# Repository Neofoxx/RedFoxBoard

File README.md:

# RedFoxBoard
A PIC32MX250 (and others) board, similar to the ubiquitous Blue Pill board

## Pinout

#### PCB view

#### Panel view

## Description 

This is a small development board, featured around a PIC32MX microcontroller.

The intent is to have a small Blue Pill-like board, that can be quickly used with an open-source toolchain for the PIC32MX (see https://gitlab.com/rhn/pic32-parts-free )

The feature list is as follows:
- USB-C connector
- Two LEDs, one Power, one User
- Two buttons, one Reset, one User
- Components only on one side
- Footprints for two 3.3V regulators (smaller or bigger, depending on your needs)
- Fits into DIP-40 socket
- Breakaway section on the PCB, with place for an ICSP or JTAG connector

The purpose of the breakaway is to have a convenient place for programming/debugging. The same pins are also exposed on the side pins. To remove the breakaway, score the vias with a knife, then break it off.

Apart from the oscillator pins, everything is connected to the side pins.

If you do not wish to use USB functionality, you can place resistors R9 and R10, and connect those pins to the side as well.

### Supported MCUs
It supports the following microcontrollers:
- PIC32MX270F256D
- PIC32MX250F128D
- PIC32MX230F256D
- PIC32MX230F064D
- PIC32MX170F256D (without USB)
- PIC32MX150F128D (without USB)
- PIC32MX130F256D (without USB)
- PIC32MX130F064D (without USB)

Additionally, the following can also be used, but ICSP pins are not available on the provided header (use the ones on the side):
- PIC32MX220F032D
- PIC32MX210F016D
- PIC32MX120F032D (without USB)
- PIC32MX110F016D (without USB)

#### Notes

Please note, there are 6mm push buttons with different spacings on the pins. Make sure to get the right ones

The series resistor with the main oscillator hasn't been checked yet

The capacitors for the 32.768kHz crystal haven't been checked yet.

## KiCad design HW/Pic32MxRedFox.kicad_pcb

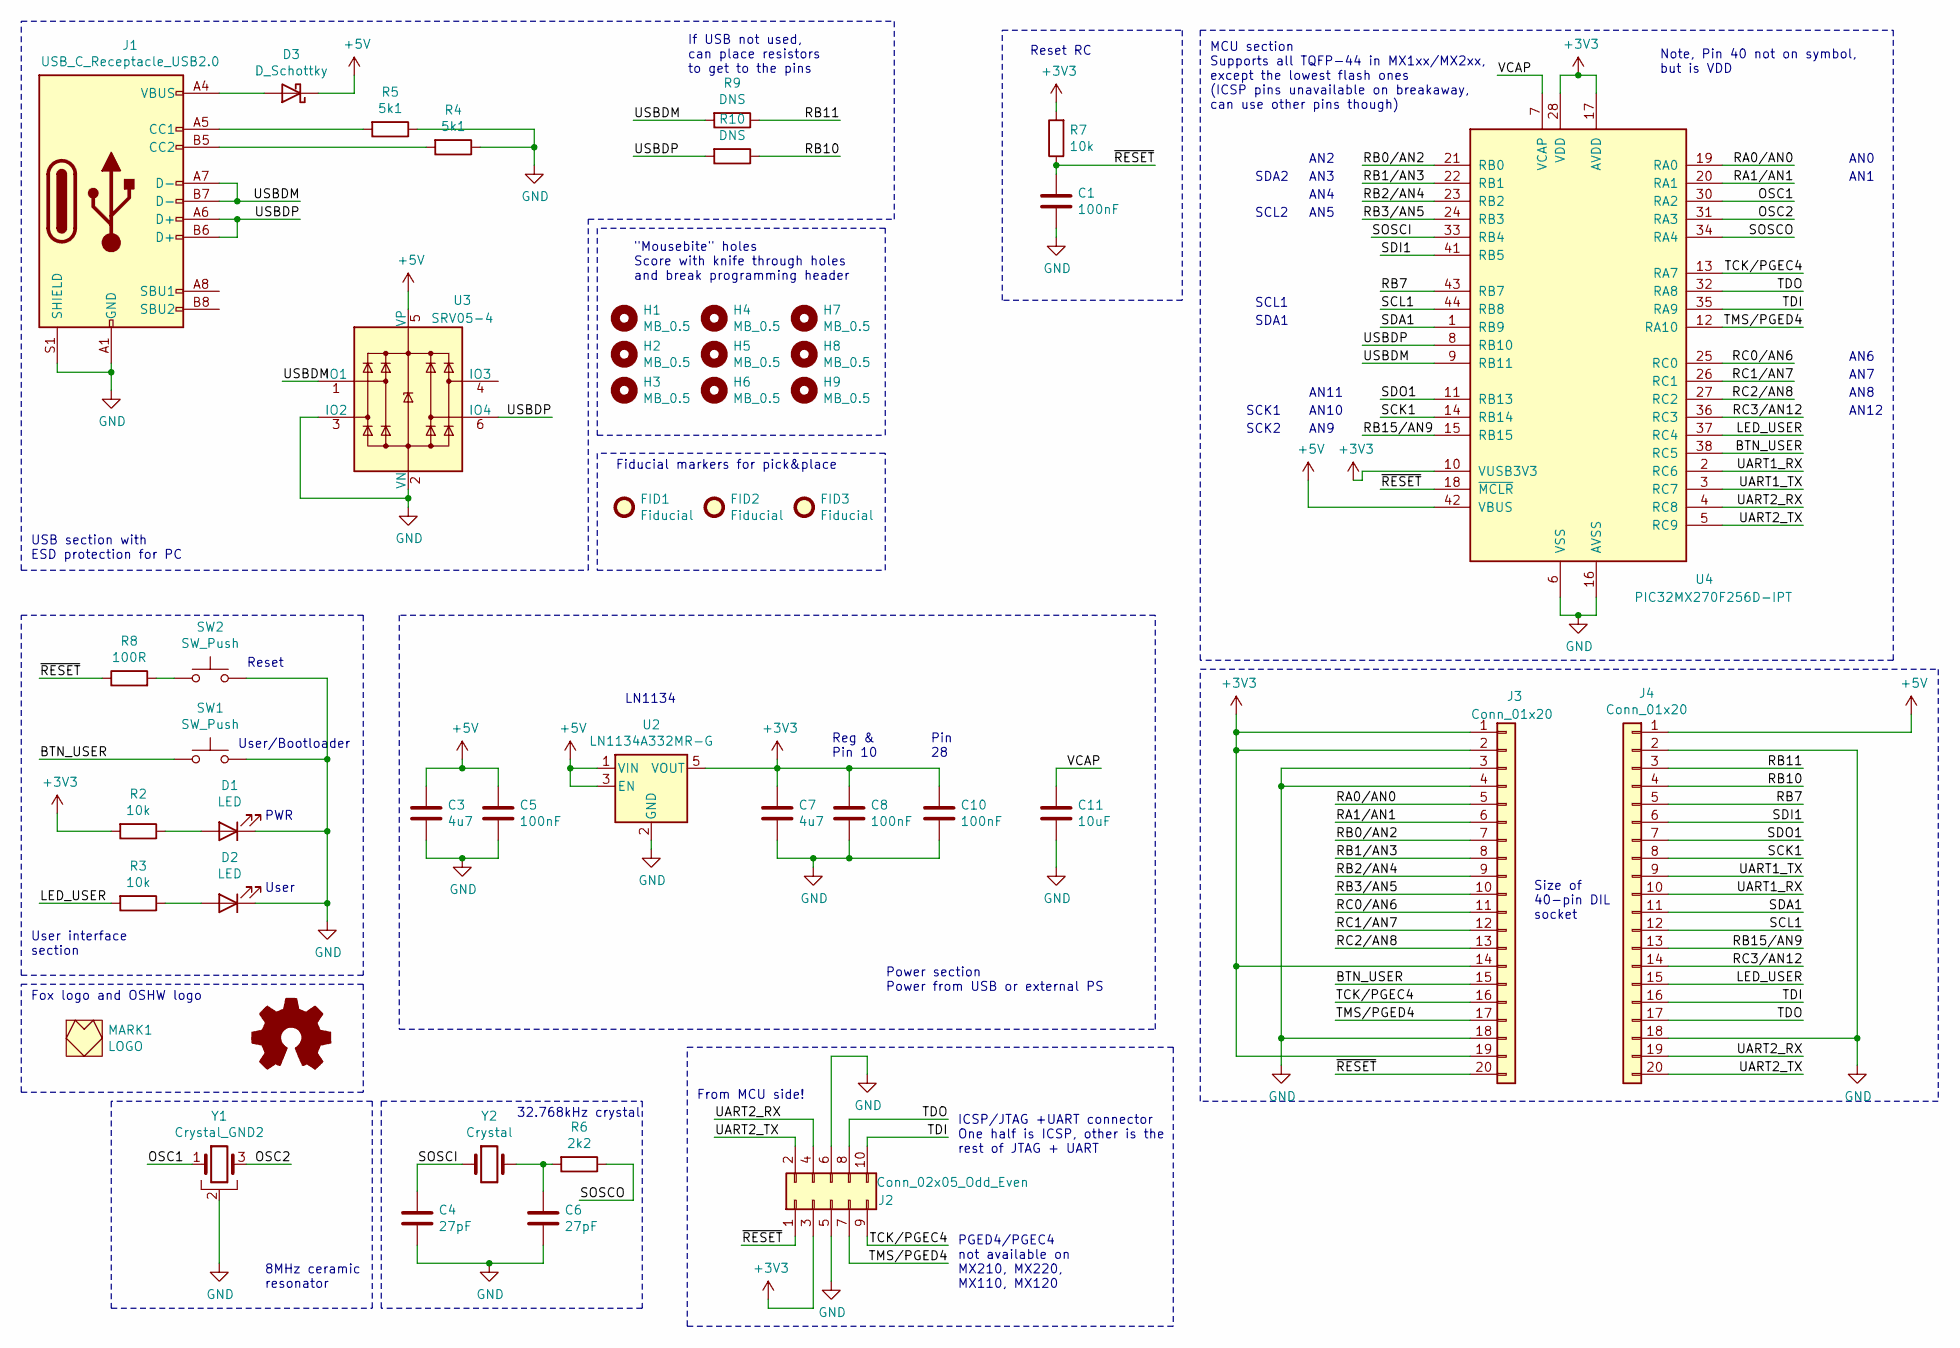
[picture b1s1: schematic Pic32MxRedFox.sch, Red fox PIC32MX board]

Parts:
C1, C5, C8, C10: 100nF; C_0603_1608Metric_Pad1.05x0.95mm_HandSolder
C3, C7: 4u7; C_0805_2012Metric_Pad1.15x1.40mm_HandSolder
C4, C6: 27pF; C_0603_1608Metric_Pad1.05x0.95mm_HandSolder
C11: 10uF; C_0805_2012Metric_Pad1.15x1.40mm_HandSolder
D1, D2: LED; LED_0603_1608Metric_Pad1.05x0.95mm_HandSolder
D3: D_Schottky; D_SOD-323_HandSoldering
FID1, FID2, FID3: Fiducial; Fiducial_0.5mm_Mask1mm
H1, H2, H3, H4, H5, H6, H7, H8, H9: MB_0.5; MouseBiteHole_0.5mm
J1: USB_C_Receptacle_USB2.0; Jing USB C 2.0 16pin receptable
J2: Conn_02x05_Odd_Even; IDC-Header_2x05_P2.54mm_Vertical
J3, J4: Conn_01x20; PinHeader_1x20_P2.54mm_Vertical
MARK1: LOGO; FOX_LOGO_MASK
MARK2: Logo_Open_Hardware_Small; OSHW-Logo_5.7x6mm_SilkScreen
R2, R3, R7: 10k; R_0603_1608Metric_Pad1.05x0.95mm_HandSolder
R4, R5: 5k1; R_0603_1608Metric_Pad1.05x0.95mm_HandSolder
R6: 2k2; R_0603_1608Metric_Pad1.05x0.95mm_HandSolder
R8: 100R; R_0603_1608Metric_Pad1.05x0.95mm_HandSolder
R9, R10: DNS; R_0603_1608Metric_Pad1.05x0.95mm_HandSolder
SW1, SW2: SW_Push; SW_SPST_B3S-1000
U2: LN1134A332MR-G; SOT-23-5
U3: SRV05-4; SOT-23-6
U4: PIC32MX270F256D-IPT; TQFP-44_10x10mm_P0.8mm
Y1: Crystal_GND2; Resonator_SMD_muRata_CSTxExxV-3Pin_3.0x1.1mm
Y2: Crystal; Crystal_SMD_3215-2Pin_3.2x1.5mm

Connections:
+3V3: C7.1, C8.1, C10.1, J2.3, J3.1, J3.2, J3.14, J3.19, R2.2, R7.2, U2.5 (VOUT), U4.10 (VUSB3V3), U4.17 (AVDD), U4.28 (VDD), U4.40 (VDD)
+5V: C3.1, C5.1, D3.1 (K), J4.1, U2.1 (VIN), U2.3 (EN), U3.5 (VP), U4.42 (VBUS)
/BTN_USER: J3.15, SW1.1, U4.38 (RC5)
/LED_USER: J4.15, R3.2, U4.37 (RC4)
/OSC1: U4.30 (RA2), Y1.1
/OSC2: U4.31 (RA3), Y1.3
/RA0/AN0: J3.5, U4.19 (RA0)
/RA1/AN1: J3.6, U4.20 (RA1)
/RB0/AN2: J3.7, U4.21 (RB0)
/RB1/AN3: J3.8, U4.22 (RB1)
/RB2/AN4: J3.9, U4.23 (RB2)
/RB3/AN5: J3.10, U4.24 (RB3)
/RB7: J4.5, U4.43 (RB7)
/RB10: J4.4, R10.1
/RB11: J4.3, R9.1
/RB15/AN9: J4.13, U4.15 (RB15)
/RC0/AN6: J3.11, U4.25 (RC0)
/RC1/AN7: J3.12, U4.26 (RC1)
/RC2/AN8: J3.13, U4.27 (RC2)
/RC3/AN12: J4.14, U4.36 (RC3)
/SCK1: J4.8, U4.14 (RB14)
/SCL1: J4.12, U4.44 (RB8)
/SDA1: J4.11, U4.1 (RB9)
/SDI1: J4.6, U4.41 (RB5)
/SDO1: J4.7, U4.11 (RB13)
/SOSCI: C4.1, U4.33 (RB4), Y2.1
/SOSCO: R6.1, U4.34 (RA4)
/TCK/PGEC4: J2.9, J3.16, U4.13 (RA7)
/TDI: J2.10, J4.16, U4.35 (RA9)
/TDO: J2.8, J4.17, U4.32 (RA8)
/TMS/PGED4: J2.7, J3.17, U4.12 (RA10)
/UART1_RX: J4.10, U4.2 (RC6)
/UART1_TX: J4.9, U4.3 (RC7)
/UART2_RX: J2.4, J4.19, U4.4 (RC8)
/UART2_TX: J2.2, J4.20, U4.5 (RC9)
/USBDM: J1.A7 (D-), J1.B7 (D-), R9.2, U3.1 (IO1), U4.9 (RB11)
/USBDP: J1.A6 (D+), J1.B6 (D+), R10.2, U3.6 (IO4), U4.8 (RB10)
/VCAP: C11.1, U4.7 (VCAP)
/~RESET~: C1.1, J2.1, J3.20, R7.1, R8.1, U4.18 (~MCLR)
GND: C1.2, C3.2, C4.2, C5.2, C6.2, C7.2, C8.2, C10.2, C11.2, D1.1 (K), D2.1 (K), J1.A1 (GND), J1.A12 (GND), J1.B1 (GND), J1.B12 (GND), J1.S1 (SHIELD), J2.5, J2.6, J3.3, J3.4, J3.18, J4.2, J4.18, R4.1, R5.1, SW1.2, SW2.2, U2.2 (GND), U3.2 (VN), U3.3 (IO2), U4.6 (VSS), U4.16 (AVSS), U4.29 (VSS), U4.39 (VSS), Y1.2
unnamed: C6.1, R6.2, Y2.2
unnamed: D1.2 (A), R2.1
unnamed: D2.2 (A), R3.1
unnamed: D3.2 (A), J1.A4 (VBUS), J1.A9 (VBUS), J1.B4 (VBUS), J1.B9 (VBUS)
unnamed: J1.A5 (CC1), R5.2
unnamed: J1.B5 (CC2), R4.2
unnamed: R8.2, SW2.1

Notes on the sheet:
Reset
User/Bootloader
PWR
User
Size of 40-pin DIL socket
ICSP/JTAG +UART connector One half is ICSP, other is the rest of JTAG + UART
From MCU side!
32.768kHz crystal
8MHz ceramic resonator
Reg & Pin 10
Pin 28
PGED4/PGEC4 not available on MX210, MX220, MX110, MX120
AN0
AN1
AN2
AN3
AN4
AN5
AN6
AN7
AN8
AN9
AN10
AN11
AN12
SDA1
SDA2
SCK1
SCK2
SCL1
SCL2
LN1134
If USB not used, can place resistors to get to the pins
User interface section
Power section Power from USB or external PS
MCU section Supports all TQFP-44 in MX1xx/MX2xx, except the lowest flash ones (ICSP pins unavailable on breakaway, can use other pins though)
Note, Pin 40 not on symbol, but is VDD
Reset RC
USB section with ESD protection for PC
"Mousebite" holes Score with knife through holes and break programming header

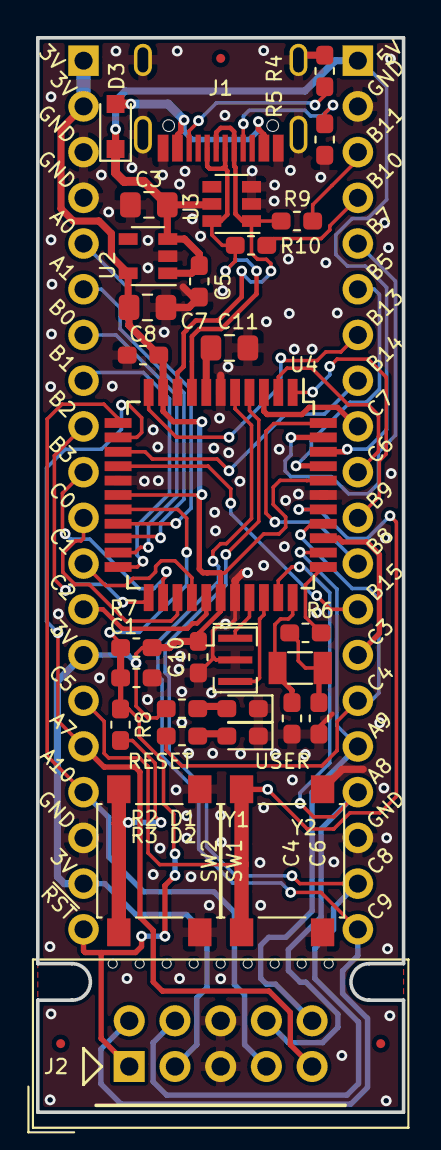
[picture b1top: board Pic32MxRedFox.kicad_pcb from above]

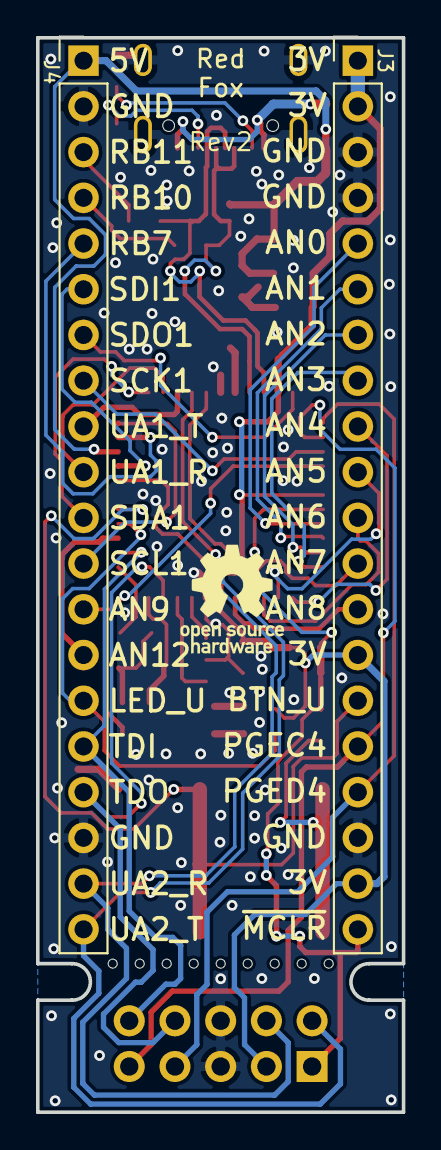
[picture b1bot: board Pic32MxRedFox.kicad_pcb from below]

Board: 2 copper layers, 20.3 x 59.7 mm, 46 parts (4 on the bottom side), 47 nets.

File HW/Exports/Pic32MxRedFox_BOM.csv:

"Source:","/home/neofoxx/Projects/HW/Gitted/RedFoxBoard/HW/Pic32MxRedFox.sch"
"Date:","pon 12 avg 2019 22:32:37 CEST"
"Tool:","Eeschema 5.0.2-bee76a0~70~ubuntu18.04.1"
"Generator:","/usr/share/kicad/plugins/bom_csv_grouped_by_value_with_fp.py"
"Component Count:","42"
"Ref","Qnty","Value","Cmp name","Footprint","Description","Vendor"
"C3, C7, ","2","4u7","C","Capacitor_SMD:C_0805_2012Metric_Pad1.15x1.40mm_HandSolder","Unpolarized capacitor",""
"C4, C6, ","2","27pF","C","Capacitor_SMD:C_0603_1608Metric_Pad1.05x0.95mm_HandSolder","Unpolarized capacitor",""
"C5, C8, C10, C9, C1, ","5","100nF","C","Capacitor_SMD:C_0603_1608Metric_Pad1.05x0.95mm_HandSolder","Unpolarized capacitor",""
"C11, ","1","10uF","C","Capacitor_SMD:C_0805_2012Metric_Pad1.15x1.40mm_HandSolder","Unpolarized capacitor",""
"D1, D2, ","2","LED","LED","LED_SMD:LED_0603_1608Metric_Pad1.05x0.95mm_HandSolder","Light emitting diode",""
"D3, ","1","D_Schottky","D_Schottky","Diode_SMD:D_SOD-323_HandSoldering","Schottky diode",""
"H1, H3, H5, H2, H4, H6, ","6","MB_0.5","MountingHole","KiCAD library:MouseBiteHole_0.5mm","Mounting Hole without connection",""
"J1, ","1","USB_C_Receptacle_USB2.0","USB_C_Receptacle_USB2.0","KiCAD library:Jing USB C 2.0 16pin receptable","USB 2.0-only Type-C Receptacle connector",""
"J2, ","1","Conn_02x05_Odd_Even","Conn_02x05_Odd_Even","Connector_IDC:IDC-Header_2x05_P2.54mm_Vertical","Generic connector, double row, 02x05, odd/even pin numbering scheme (row 1 odd numbers, row 2 even numbers), script generated (kicad-library-utils/schlib/autogen/connector/)",""
"J3, J4, ","2","Conn_01x20","Conn_01x20","Connector_PinHeader_2.54mm:PinHeader_1x20_P2.54mm_Vertical","Generic connector, single row, 01x20, script generated (kicad-library-utils/schlib/autogen/connector/)",""
"MARK1, ","1","LOGO","LOGO","KiCAD library:FOX_LOGO_MASK","",""
"R1, ","1","0R","R","Resistor_SMD:R_0603_1608Metric_Pad1.05x0.95mm_HandSolder","Resistor",""
"R2, R3, ","2","1k","R","Resistor_SMD:R_0603_1608Metric_Pad1.05x0.95mm_HandSolder","Resistor",""
"R4, R5, ","2","5k1","R","Resistor_SMD:R_0603_1608Metric_Pad1.05x0.95mm_HandSolder","Resistor",""
"R6, ","1","2k2","R","Resistor_SMD:R_0603_1608Metric_Pad1.05x0.95mm_HandSolder","Resistor",""
"R7, ","1","10k","R","Resistor_SMD:R_0603_1608Metric_Pad1.05x0.95mm_HandSolder","Resistor",""
"R8, ","1","100R","R","Resistor_SMD:R_0603_1608Metric_Pad1.05x0.95mm_HandSolder","Resistor",""
"R9, R10, ","2","DNS","R","Resistor_SMD:R_0603_1608Metric_Pad1.05x0.95mm_HandSolder","Resistor",""
"SW1, SW2, ","2","SW_Push","SW_Push","Button_Switch_SMD:SW_SPST_B3S-1000","Push button switch, generic, two pins",""
"U1, ","1","LD1117S33TR_SOT223","LD1117S33TR_SOT223","Package_TO_SOT_SMD:SOT-223-3_TabPin2","800mA Fixed Low Drop Positive Voltage Regulator, Fixed Output 3.3V, SOT-223",""
"U2, ","1","LN1134A332MR-G","AP2204K-3.3","Package_TO_SOT_SMD:SOT-23-5","150mA low dropout linear regulator, wide input voltage range, 3.3V fixed positive output, SOT-23-5 package",""
"U3, ","1","SRV05-4","SRV05-4","Package_TO_SOT_SMD:SOT-23-6","ESD Protection Diodes with Low Clamping Voltage, SOT-23-6",""
"U4, ","1","PIC32MX270F256D-IPT","PIC32MX270F256D-IPT","Package_QFP:TQFP-44_10x10mm_P0.8mm","32-bit Microcontrollers (256KB Flash and 64KB SRAM TQFP-44) with Audio and Graphics Interfaces, USB, and Advanced Analog",""
"Y1, ","1","Crystal_GND2","Crystal_GND2","Crystal:Resonator_SMD_muRata_CSTxExxV-3Pin_3.0x1.1mm","Three pin crystal, GND on pin 2",""
"Y2, ","1","Crystal","Crystal","Crystal:Crystal_SMD_3215-2Pin_3.2x1.5mm","Two pin crystal",""

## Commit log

2019-08-12 First commit of the Rev1 files of the RedFox board
2019-08-12 Eliminate rouge mouse cursor
2021-01-13 Rev2 of board, now actually fits in DIP40 socket...
2021-01-17 New revision that actually fits in a DIP40 socket. Pinout stays the same.
2021-01-17 Remove unintended file
